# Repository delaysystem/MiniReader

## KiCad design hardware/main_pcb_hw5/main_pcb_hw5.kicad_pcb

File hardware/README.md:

# SANNI Adapters aren't compatible with MiniReader Adapters

## All the files in this directory are licensed under the Attribution 4.0 International (CC BY 4.0)     

### This means that you are free to:    
- Share - copy and redistribute the material in any medium or format    
- Adapt - remix, transform, and build upon the material for any purpose, even commercially.  

The licensor cannot revoke these freedoms as long as you follow the license terms.    

### Under the following terms:    
- Attribution - You must give appropriate credit, provide a link to the license, and indicate if changes were made. You may do so in any reasonable manner, but not in any way that suggests the licensor endorses you or your use.    
- No additional restrictions - You may not apply legal terms or technological measures that legally restrict others from doing anything the license permits.    

More details: https://creativecommons.org/licenses/by/4.0/

##

You can view the schematic and PCB files using [KiCad](https://www.kicad.org/).   
To design your own adapters you can follow this [tutorial](https://github.com/sanni/cartreader/wiki/Designing-your-own-Adapters)   
Also check out the user contributions for even more adapters: https://github.com/sanni/cartreader/discussions/354

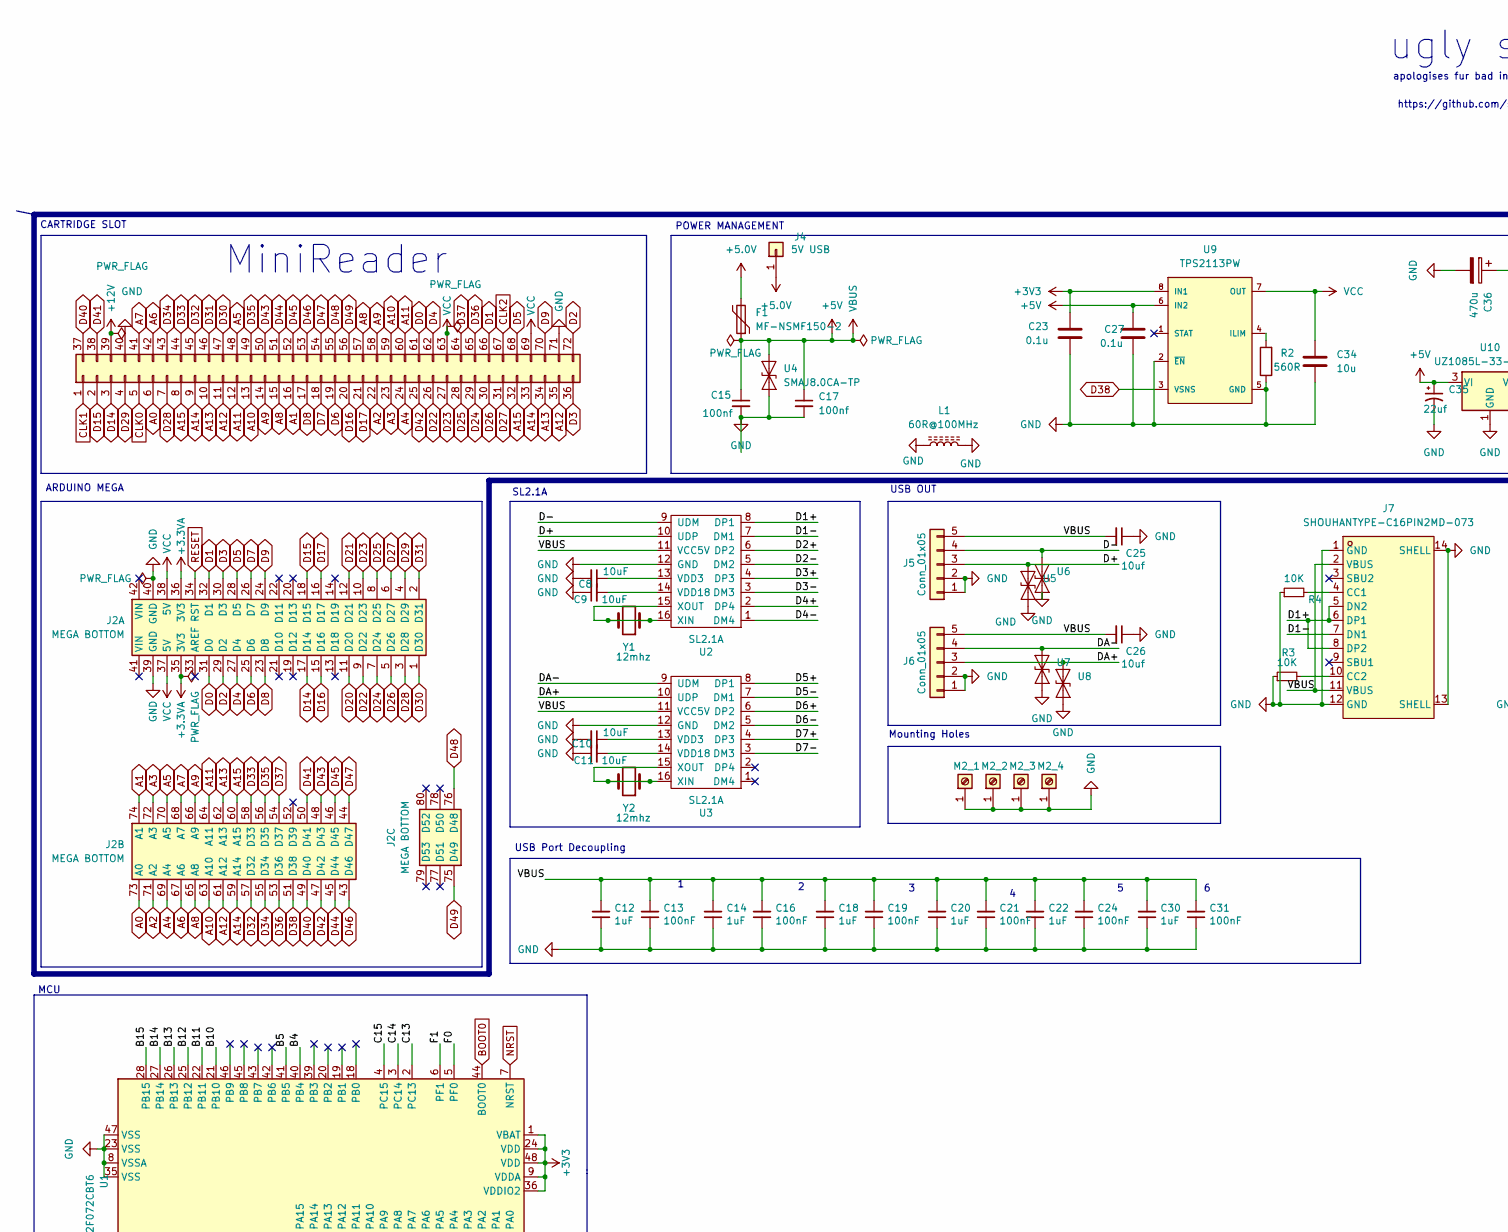
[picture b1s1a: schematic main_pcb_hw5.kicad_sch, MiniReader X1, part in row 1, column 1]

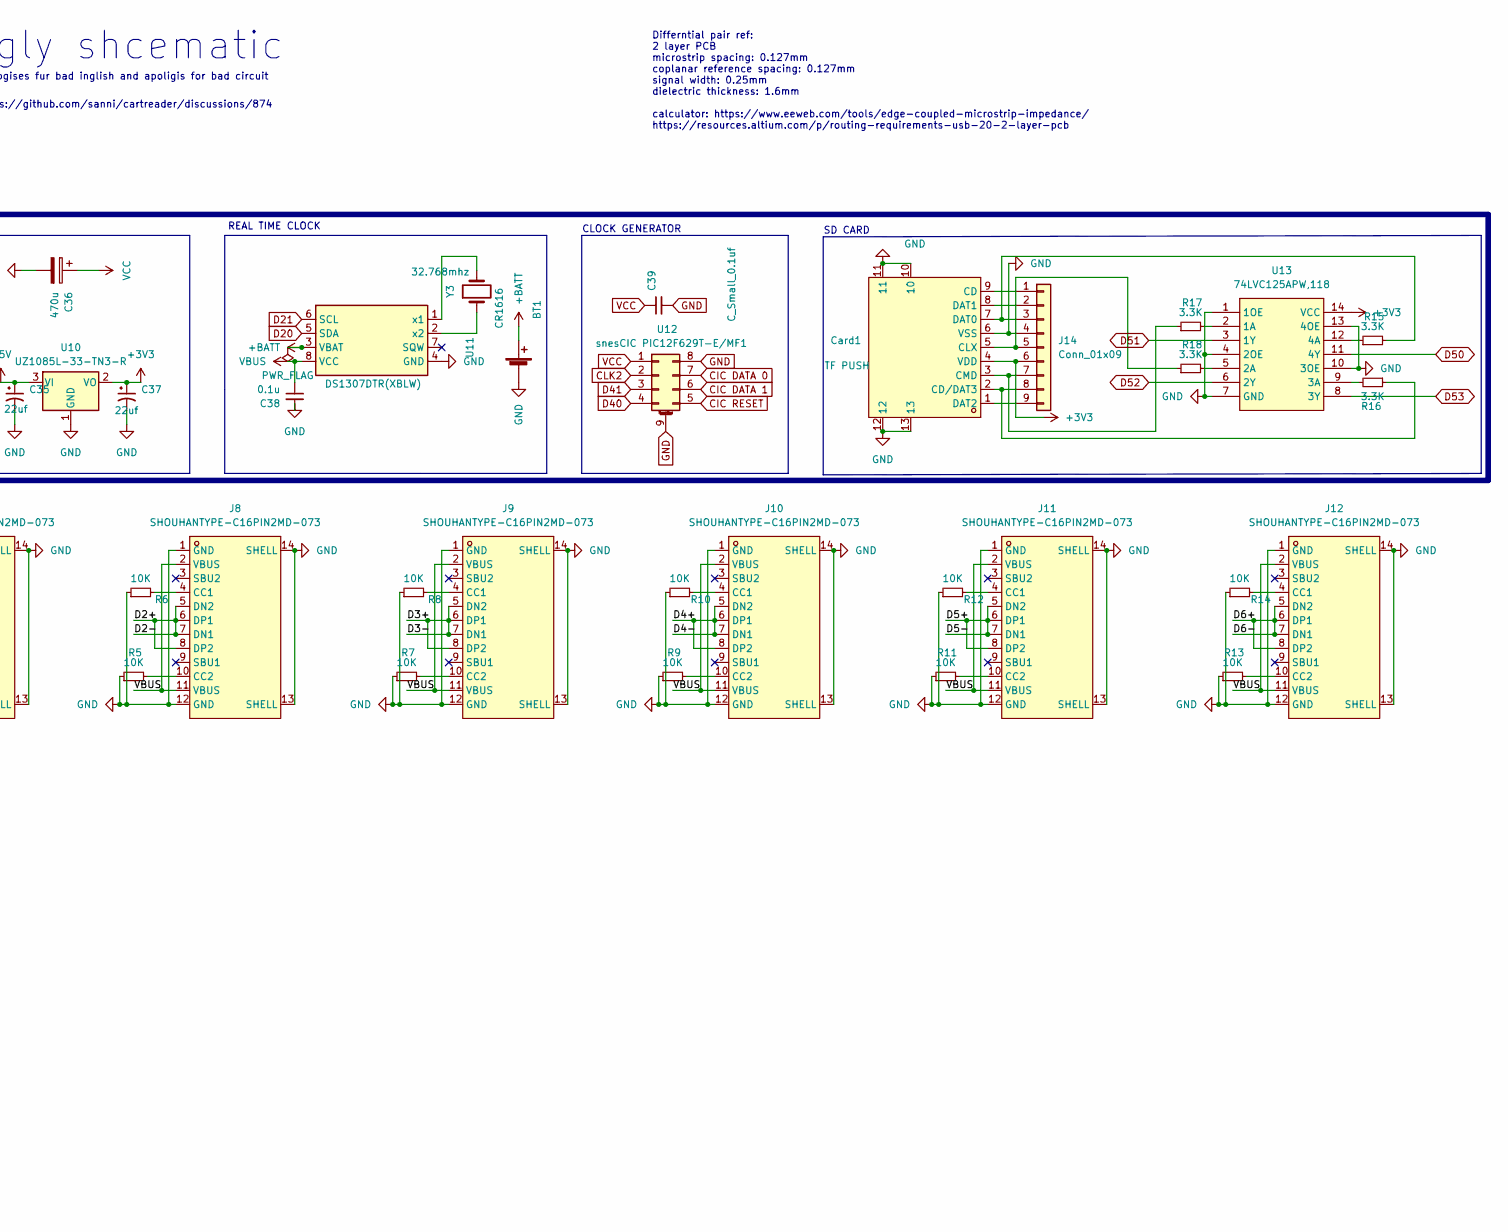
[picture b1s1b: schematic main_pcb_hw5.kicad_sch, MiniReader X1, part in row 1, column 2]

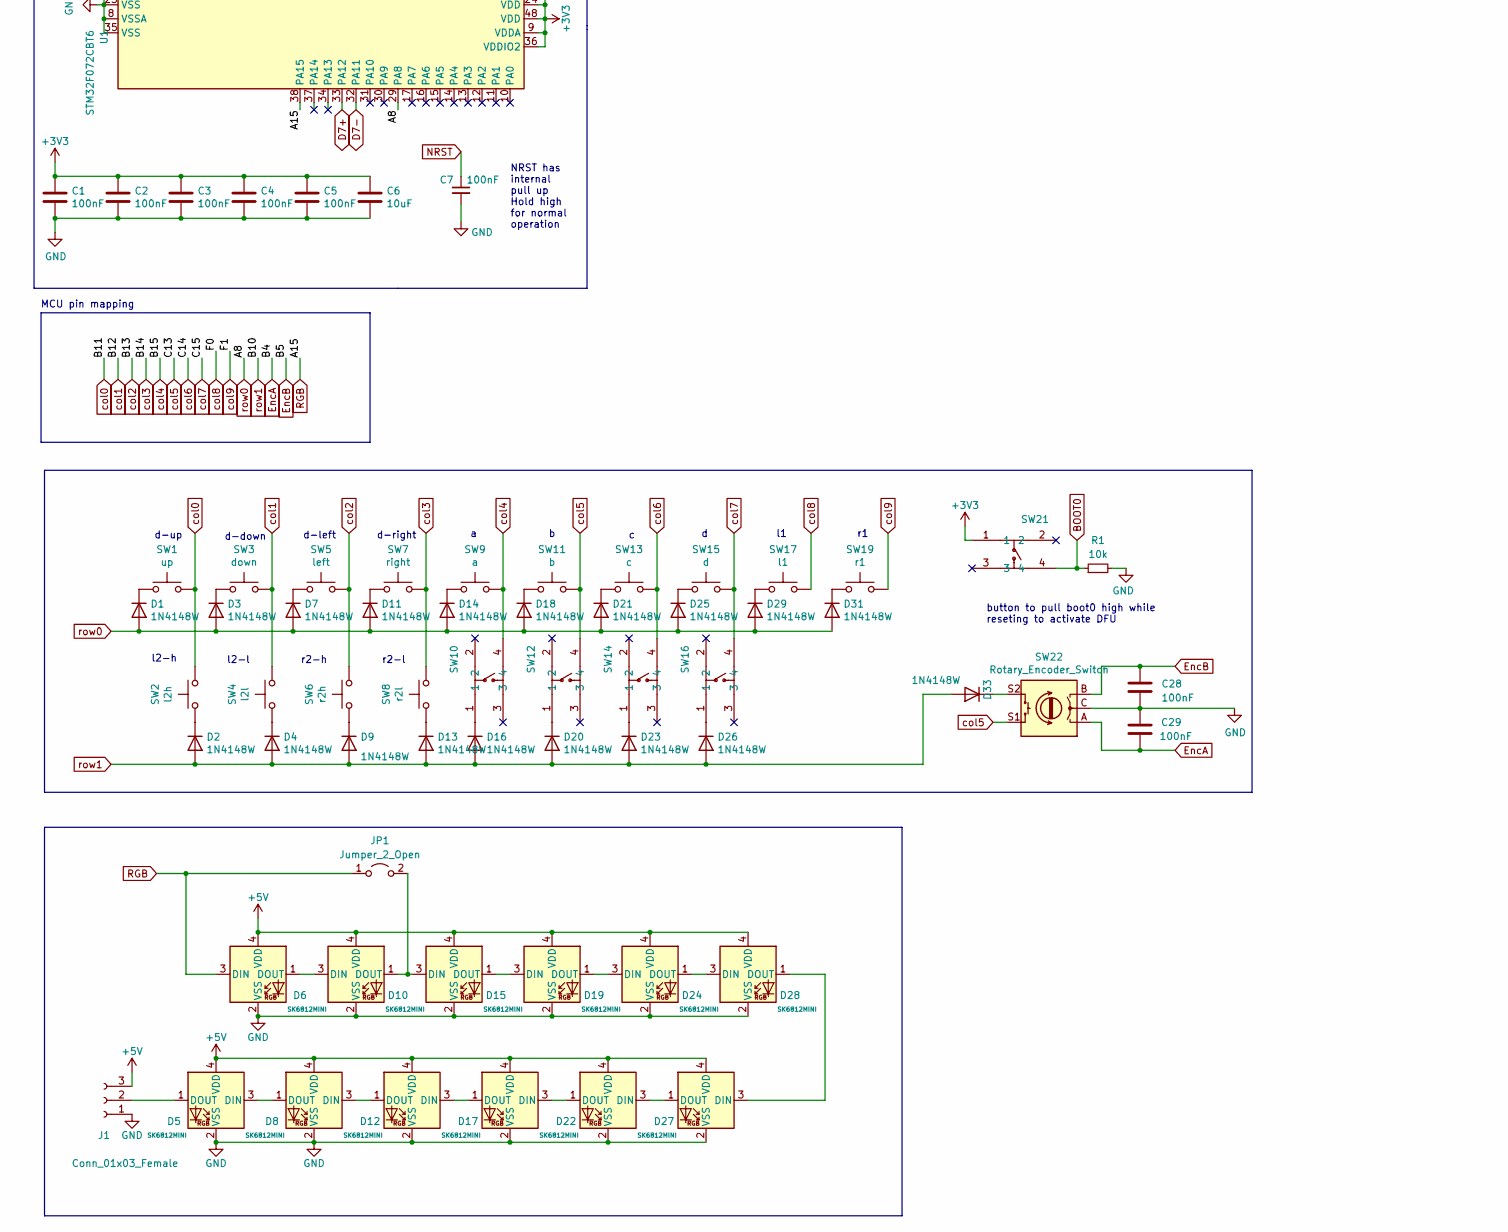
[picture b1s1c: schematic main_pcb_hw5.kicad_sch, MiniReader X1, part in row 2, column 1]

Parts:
BT1: CR1616
C1, C2, C3, C4, C5, C7, C28, C29: 100nF; C_0805_2012Metric; LCSC C307331
C6, C8, C9, C10, C11: 10uF; C_0805_2012Metric
C12, C14, C18, C20, C22, C30: 1uF; C_0805_2012Metric
C13, C16, C19, C21, C24, C31: 100nF; C_0805_2012Metric
C15, C17: 100nf; C_0805_2012Metric
C23, C27, C38: 0.1u; C_0805_2012Metric; JLCPCB C307331
C25, C26: 10uf; C_0805_2012Metric
C34: 10u; C_0805_2012Metric; JLCPCB C15525
C35, C37: 22uf; C_0805_2012Metric
C36: 470u; CP_EIA-7343-31_Kemet-D
C39: C_Small_0.1uf; C_0805_2012Metric
Card1: TF PUSH; TF-SMD_TF-PUSH; LCSC Part C393941
D1, D2, D3, D4, D7, D9, D11, D13, D14, D16, D20, D23, D26: 1N4148W; D_SOD-123; JlcRotOffset 14
D5, D12, D17: SK6812MINI; LED_SK6812MINI_PLCC4_3.5x3.5mm_P1.75mm; JlcRotOffset 14
D6, D10: SK6812MINI; LED_SK6812MINI_PLCC4_3.5x3.5mm_P1.75mm
D8: SK6812MINI; LED_SK6812MINI_PLCC4_3.5x3.5mm_P1.75mm; JlcRotOffset 194
D15, D24, D27, D28: SK6812MINI; LED_SK6812MINI_PLCC4_3.5x3.5mm_P1.75mm; JlcRotOffset -14
D18, D21, D25, D29, D31: 1N4148W; D_SOD-123; JlcRotOffset -14
D19: SK6812MINI; LED_SK6812MINI_PLCC4_3.5x3.5mm_P1.75mm; JlcRotOffset 166
D22: SK6812MINI; LED_SK6812MINI_PLCC4_3.5x3.5mm_P1.75mm; JlcRotOffset 180
D33: 1N4148W; D_SOD-123; JlcRotOffset 0
F1: MF-NSMF150-2; Fuse_1206_3216Metric; LCSC C135341
J1: Conn_01x03_Female; PinSocket_1x03_P2.54mm_Vertical
J2: MEGA BOTTOM; MEGA2560_PRO_EMBED_SMD
J3: Conn_02x36; Secondary_Board_Connector
J4: 5V USB; TestPoint_Pad_D2.0mm
J5, J6: Conn_01x05; PinHeader_1x05_P1.00mm_Vertical
J7, J8, J9, J10, J11, J12: SHOUHANTYPE-C16PIN2MD-073; USB-C-SMD_TYPE-C-6PIN-2MD-073; PARTREV 4; LCSC Part C2765186
J14: Conn_01x09; PinHeader_1x09_P1.00mm_Vertical
JP1: Jumper_2_Open; SolderJumper-2_P1.3mm_Open_TrianglePad1.0x1.5mm
L1: 60R@100MHz; L_1206_3216Metric; Manufacturer Part No MLB3216-600P4A(f); LCSC C33600
M2_1, M2_2, M2_3, M2_4: Screw_Terminal_01x01; MountingHole_2.2mm_M2_ISO7380_Pad
R1: 10k; R_0805_2012Metric
R2: 560R; R_0805_2012Metric; JLCPCB C137858
R3, R4, R5, R6, R7, R8, R9, R10, R11, R12, R13, R14: 10K; R_0805_2012Metric
R15, R16, R17, R18: 3.3K; R_0805_2012Metric
SW1: up; MX-Hotswap-1U
SW2: l2h; MX-Hotswap-1U
SW3: down; MX-Hotswap-1U
SW4: l2l; MX-Hotswap-1U
SW5: left; MX-Hotswap-1U
SW6: r2h; MX-Hotswap-1U
SW7: right; MX-Hotswap-1U
SW8: r2l; MX-Hotswap-1U
SW9: a; MX-Hotswap-1U
SW10, SW12, SW14, SW16, SW21: SKQGABE010; SW-SMD_4P-L4.5-W4.5-P3.00-LS6.8; LCSC C115351
SW11: b; MX-Hotswap-1U
SW13: c; MX-Hotswap-1U
SW15: d; MX-Hotswap-1U
SW17: l1; MX-Hotswap-1U
SW19: r1; MX-Hotswap-1U
SW22: Rotary_Encoder_Switch; RotaryEncoder_EC11_no_mp
U1: STM32F072CBT6; LQFP-48_7x7mm_P0.5mm; JlcRotOffset 90
U2, U3: SL2.1A; SOIC-16_4.55x10.3mm_P1.27mm
U4, U5, U6, U7, U8: SMAJ8.0CA-TP; D_SMA
U9: TPS2113PW; TSSOP-8_4.4x3mm_P0.65mm
U10: UZ1085L-33-TN3-R; TO-252-2
U11: DS1307DTR(XBLW); SOIC-8_3.9x4.9mm_P1.27mm
U12: snesCIC PIC12F629T-E/MF1; DFN-8-1EP_4x4mm_P0.8mm_EP2.39x2.21mm
U13: 74LVC125APW,118; TSSOP-14_L5.0-W4.4-P0.65-LS6.4-BL; LCSC Part C6059
Y1, Y2: 12mhz; Crystal_HC49-4H_Vertical
Y3: 32.768mhz; Crystal_HC49-4H_Vertical

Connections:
+3.3VA: J2.35 (3V3), J2.36 (3V3)
+3V3: C1.1, C2.1, C3.1, C4.1, C5.1, C6.1, C23.2, C37.1, Card1.4 (VDD), J14.6, SW21.1, U1.1 (VBAT), U1.9 (VDDA), U1.24 (VDD), U1.36 (VDDIO2), U1.48 (VDD), U9.8 (IN1), U10.2 (VO), U13.14 (VCC)
+5.0V: F1.2, J4.1
+5V: C12.2, C13.2, C14.2, C15.1, C16.2, C17.1, C18.2, C19.2, C20.2, C21.2, C22.2, C24.2, C25.2, C26.2, C27.1, C30.2, C31.2, C35.1, C38.1, D5.4 (VDD), D6.4 (VDD), D8.4 (VDD), D10.4 (VDD), D12.4 (VDD), D15.4 (VDD), D17.4 (VDD), D19.4 (VDD), D22.4 (VDD), D24.4 (VDD), D27.4 (VDD), D28.4 (VDD), F1.1, J1.3 (Pin_1), J5.5, J6.5, J7.2 (VBUS), J7.11 (VBUS), J8.2 (VBUS), J8.11 (VBUS), J9.2 (VBUS), J9.11 (VBUS), J10.2 (VBUS), J10.11 (VBUS), J11.2 (VBUS), J11.11 (VBUS), J12.2 (VBUS), J12.11 (VBUS), U2.11 (VCC5V), U3.11 (VCC5V), U4.2 (A2), U9.6 (IN2), U10.3 (VI), U11.8 (VCC)
+12V: J3.39
+BATT: BT1.1 (+), U11.3 (VBAT)
/D1+: J7.5 (DN2), J7.6 (DP1), J7.8 (DP2), U2.8 (DP1)
/D1-: J7.7 (DN1), U2.7 (DM1)
/D2+: J8.5 (DN2), J8.6 (DP1), J8.7 (DN1), J8.8 (DP2), U2.5 (DM2), U2.6 (DP2)
/D3+: J9.5 (DN2), J9.6 (DP1), J9.7 (DN1), J9.8 (DP2), U2.3 (DM3), U2.4 (DP3)
/D4+: J10.5 (DN2), J10.6 (DP1), J10.7 (DN1), J10.8 (DP2), U2.1 (DM4), U2.2 (DP4)
/D5+: J11.5 (DN2), J11.6 (DP1), J11.7 (DN1), J11.8 (DP2), U3.7 (DM1), U3.8 (DP1)
/D6+: J12.5 (DN2), J12.6 (DP1), J12.7 (DN1), J12.8 (DP2), U3.5 (DM2), U3.6 (DP2)
/D+: J5.3, U2.10 (UDP), U5.2 (A2)
/D-: J5.4, U2.9 (UDM), U6.2 (A2)
/DA+: J6.3, U3.10 (UDP), U8.2 (A2)
/DA-: J6.4, U3.9 (UDM), U7.2 (A2)
A0: J2.73 (A0), J3.6
A1: J2.74 (A1), J3.16
A2: J2.71 (A2), J3.22
A3: J2.72 (A3), J3.23
A4: J2.69 (A4), J3.24
A5: J2.70 (A5), J3.48
A6: J2.67 (A6), J3.42
A7: J2.68 (A7), J3.41
A8: D1.2 (A), D3.2 (A), D7.2 (A), D11.2 (A), D14.2 (A), D18.2 (A), D21.2 (A), D25.2 (A), D29.2 (A), D31.2 (A), J2.65 (A8), J3.15, J3.57, U1.29 (PA8)
A9: J2.66 (A9), J3.14, J3.58
A10: J2.63 (A10), J3.13, J3.59
A11: J2.64 (A11), J3.12, J3.60
A12: J2.61 (A12), J3.11, J3.35
A13: J2.62 (A13), J3.10, J3.34
A14: J2.59 (A14), J3.9, J3.33
A15: D6.3 (DIN), J2.60 (A15), J3.8, J3.32, JP1.1 (A), U1.38 (PA15)
BOOT0: R1.1, SW21.4, U1.44 (BOOT0)
CIC DATA 0: U12.7
CIC DATA 1: U12.6
CIC RESET: U12.5
CLK0: J3.5
CLK1: J3.1
CLK2: J3.67, U12.2
D0: J2.31 (D0), J3.61
D1: J2.32 (D1), J3.66
D2: J2.29 (D2), J3.72
D3: J2.30 (D3), J3.36
D4: J2.27 (D4), J3.62
D5: J2.28 (D5), J3.68
D6: J2.25 (D6), J3.19
D7: J2.26 (D7), J3.18
D7+: U1.33 (PA12), U3.4 (DP3)
D7-: U1.32 (PA11), U3.3 (DM3)
D8: J2.23 (D8), J3.17
D9: J2.24 (D9), J3.70
D14: J2.17 (D14), J3.3
D15: J2.18 (D15), J3.2
D16: J2.15 (D16), J3.20
D17: J2.16 (D17), J3.21
D20: J2.11 (D20), U11.5 (SDA)
D21: J2.12 (D21), U11.6 (SCL)
D22: J2.9 (D22), J3.26
D23: J2.10 (D23), J3.27
D24: J2.7 (D24), J3.29
D25: J2.8 (D25), J3.28
D26: J2.5 (D26), J3.30
D27: J2.6 (D27), J3.31
D28: J2.3 (D28), J3.7
D29: J2.4 (D29), J3.4
D30: J2.1 (D30), J3.47
D31: J2.2 (D31), J3.46
D32: J2.57 (D32), J3.45
D33: J2.58 (D33), J3.44
D34: J2.55 (D34), J3.43
D35: J2.56 (D35), J3.49
D36: J2.53 (D36), J3.65
D37: J2.54 (D37), J3.64
D38: J2.51 (D38), U9.3 (VSNS)
D40: J2.49 (D40), J3.37, U12.4
D41: J2.50 (D41), J3.38, U12.3
D42: J2.47 (D42), J3.25
D43: J2.48 (D43), J3.50
D44: J2.45 (D44), J3.51
D45: J2.46 (D45), J3.52
D46: J2.43 (D46), J3.53
D47: J2.44 (D47), J3.54
D48: J2.76 (D48), J3.55
D49: J2.75 (D49), J3.56
D50: U13.11 (4Y)
D51: U13.3 (1Y)
D52: U13.6 (2Y)
D53: U13.8 (3Y)
EncA: C29.1, SW22.A, U1.40 (PB4)
EncB: C28.1, SW22.B, U1.41 (PB5)
GND: BT1.2 (-), C1.2, C2.2, C3.2, C4.2, C5.2, C6.2, C7.2, C8.2, C9.1, C10.2, C11.1, C12.1, C13.1, C14.1, C15.2, C16.1, C17.2, C18.1, C19.1, C20.1, C21.1, C22.1, C23.1, C24.1, C25.1, C26.1, C27.2, C28.2, C29.2, C30.1, C31.1, C34.2, C35.2, C36.2, C37.2, C38.2, C39.2, Card1.6 (VSS), Card1.10, Card1.11, Card1.12, Card1.13, D5.2 (VSS), D6.2 (VSS), D8.2 (VSS), D10.2 (VSS), D12.2 (VSS), D15.2 (VSS), D17.2 (VSS), D19.2 (VSS), D22.2 (VSS), D24.2 (VSS), D27.2 (VSS), D28.2 (VSS), J1.1 (Pin_3), J2.39 (GND), J2.40 (GND), J3.40, J3.71, J5.1, J5.2, J6.1, J6.2, J7.1 (GND), J7.12 (GND), J7.13 (SHELL), J7.14 (SHELL), J8.1 (GND), J8.12 (GND), J8.13 (SHELL), J8.14 (SHELL), J9.1 (GND), J9.12 (GND), J9.13 (SHELL), J9.14 (SHELL), J10.1 (GND), J10.12 (GND), J10.13 (SHELL), J10.14 (SHELL), J11.1 (GND), J11.12 (GND), J11.13 (SHELL), J11.14 (SHELL), J12.1 (GND), J12.12 (GND), J12.13 (SHELL), J12.14 (SHELL), J14.4, L1.1, L1.2, M2_1.1, M2_2.1, M2_3.1, M2_4.1, R1.2, R2.1, R3.1, R4.1, R5.1, R6.1, R7.1, R8.1, R9.1, R10.1, R11.1, R12.1, R13.1, R14.1, SW22.C, U1.8 (VSSA), U1.23 (VSS), U1.35 (VSS), U1.47 (VSS), U2.12 (GND), U3.12 (GND), U4.1 (A1), U5.1 (A1), U6.1 (A1), U7.1 (A1), U8.1 (A1), U9.2 (~EN), U9.5 (GND), U10.1 (GND), U11.4 (GND), U12.8, U12.9 (MountPin), U13.1 (1OE), U13.4 (2OE), U13.7 (GND), U13.10 (3OE), U13.13 (4OE)
NRST: C7.1, U1.7 (NRST)
unnamed: Card1.9 (CD), J14.1
unnamed: Card1.2 (CD/DAT3), J14.8, R16.1
unnamed: Card1.5 (CLX), J14.5, R18.1
unnamed: Card1.3 (CMD), J14.7, R17.1
unnamed: Card1.7 (DAT0), J14.3, R15.2
unnamed: Card1.8 (DAT1), J14.2
unnamed: Card1.1 (DAT2), J14.9
unnamed: D1.1 (K), SW1.1
unnamed: D2.1 (K), SW2.1
unnamed: D3.1 (K), SW3.1
unnamed: D4.1 (K), SW4.1
unnamed: D5.3 (DIN), D8.1 (DOUT)
unnamed: D5.1 (DOUT), J1.2
unnamed: D7.1 (K), SW5.1
unnamed: D9.1 (K), SW6.1
unnamed: D6.1 (DOUT), D10.3 (DIN)
unnamed: D10.1 (DOUT), D15.3 (DIN), JP1.2 (B)
unnamed: D11.1 (K), SW7.1
unnamed: D12.3 (DIN), D17.1 (DOUT)
unnamed: D8.3 (DIN), D12.1 (DOUT)
unnamed: D13.1 (K), SW8.1
unnamed: D14.1 (K), SW9.1
unnamed: D15.1 (DOUT), D19.3 (DIN)
unnamed: D16.1 (K), SW10.1
unnamed: D17.3 (DIN), D22.1 (DOUT)
unnamed: D18.1 (K), SW11.1
unnamed: D19.1 (DOUT), D24.3 (DIN)
unnamed: D20.1 (K), SW12.1
unnamed: D21.1 (K), SW13.1
unnamed: D22.3 (DIN), D27.1 (DOUT)
unnamed: D23.1 (K), SW14.1
unnamed: D24.1 (DOUT), D28.3 (DIN)
unnamed: D25.1 (K), SW15.1
unnamed: D26.1 (K), SW16.1
unnamed: D27.3 (DIN), D28.1 (DOUT)
unnamed: D29.1 (K), SW17.1
unnamed: D31.1 (K), SW19.1
unnamed: D33.1 (K), SW22.S2
unnamed: J7.4 (CC1), R4.2
unnamed: J7.10 (CC2), R3.2
unnamed: J8.4 (CC1), R6.2
unnamed: J8.10 (CC2), R5.2
unnamed: J9.4 (CC1), R8.2
unnamed: J9.10 (CC2), R7.2
unnamed: J10.4 (CC1), R10.2
unnamed: J10.10 (CC2), R9.2
unnamed: J11.4 (CC1), R12.2
unnamed: J11.10 (CC2), R11.2
unnamed: J12.4 (CC1), R14.2
unnamed: J12.10 (CC2), R13.2
unnamed: C8.1, U2.13 (VDD3)
unnamed: C9.2, U2.14 (VDD18)
unnamed: U2.15 (XOUT), U2.16 (XIN), Y1.1, Y1.2
unnamed: C10.1, U3.13 (VDD3)
unnamed: C11.2, U3.14 (VDD18)
unnamed: U3.15 (XOUT), U3.16 (XIN), Y2.1, Y2.2
unnamed: R2.2, U9.4 (ILIM)
unnamed: U11.1 (x1), Y3.2
unnamed: U11.2 (x2), Y3.1
unnamed: R17.2, U13.2 (1A)
unnamed: R18.2, U13.5 (2A)
unnamed: R16.2, U13.9 (3A)
unnamed: R15.1, U13.12 (4A)
RESET: J2.34 (RST)
VCC: C34.1, C36.1, C39.1, J2.37 (5V), J2.38 (5V), J3.63, J3.69, U9.7 (OUT), U12.1
col0: SW1.2, SW2.2, U1.22 (PB11)
col1: SW3.2, SW4.2, U1.25 (PB12)
col2: SW5.2, SW6.2, U1.26 (PB13)
col3: SW7.2, SW8.2, U1.27 (PB14)
col4: SW9.2, SW10.4, U1.28 (PB15)
col5: SW11.2, SW12.4, SW22.S1, U1.2 (PC13)
col6: SW13.2, SW14.4, U1.3 (PC14)
col7: SW15.2, SW16.4, U1.4 (PC15)
col8: SW17.2, U1.5 (PF0)
col9: SW19.2, U1.6 (PF1)
row1: D2.2 (A), D4.2 (A), D9.2 (A), D13.2 (A), D16.2 (A), D20.2 (A), D23.2 (A), D26.2 (A), D33.2 (A), U1.21 (PB10)

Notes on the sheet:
SD CARD
r2-h
SL2.1A
d-up
NRST has internal pull up Hold high for normal operation
l2-h
REAL TIME CLOCK
button to pull boot0 high while reseting to activate DFU
CLOCK GENERATOR
r2-l
MCU
Differntial pair ref: 2 layer PCB microstrip spacing: 0.127mm coplanar reference spacing: 0.127mm signal width: 0.25mm dielectric thickness: 1.6mm calculator: https://www.eeweb.com/tools/edge-coupled-microstrip-impedance/ https://resources.altium.com/p/routing-requirements-usb-20-2-layer-pcb
d-down
https://github.com/sanni/cartreader/discussions/874
MiniReader
d-left
POWER MANAGEMENT
ARDUINO MEGA
ugly shcematic
MCU pin mapping
Mounting Holes
apologises fur bad inglish and apoligis for bad circuit
l2-l
USB OUT
CARTRIDGE SLOT
USB Port Decoupling
d-right

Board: 2 copper layers, 144 parts (48 on the bottom side), 158 nets, no tracks yet.

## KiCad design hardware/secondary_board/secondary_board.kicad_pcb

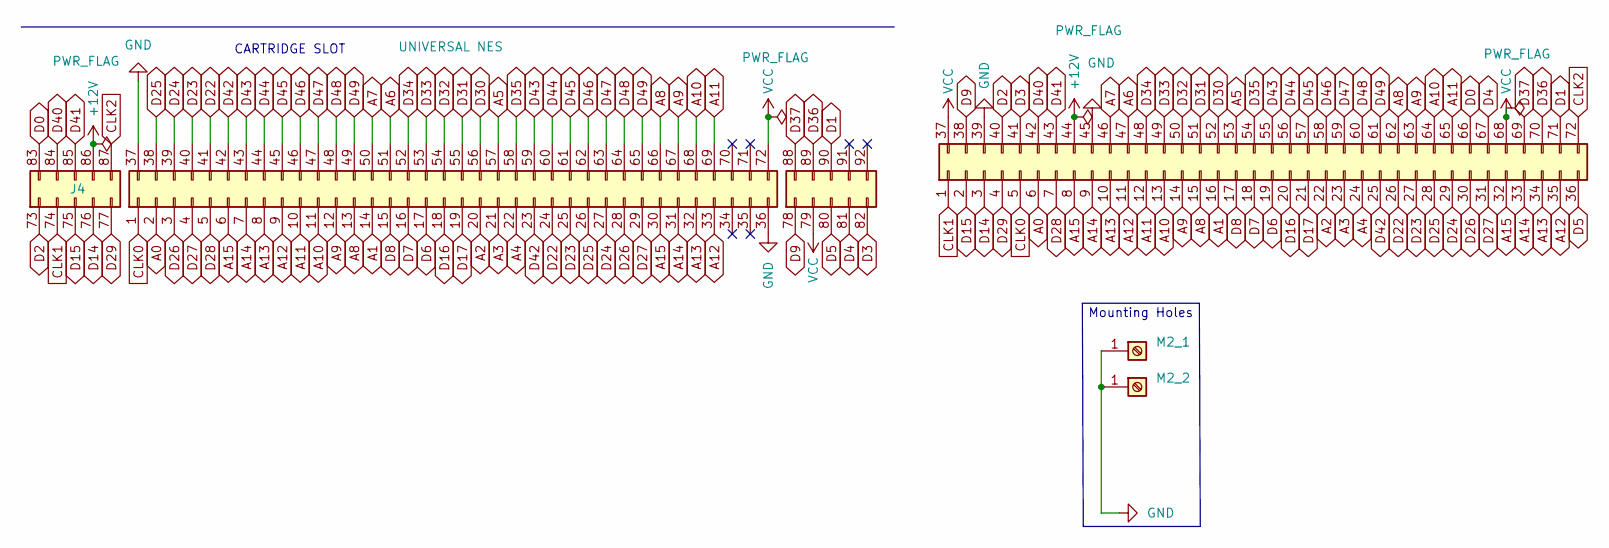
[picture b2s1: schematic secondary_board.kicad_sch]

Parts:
J1: Conn_01x72; PinHeader_1x72_P1.00mm_Vertical
J4: UNIVERSAL NES; UNIVERSAL_NES
M2_1, M2_2: Screw_Terminal_01x01; MountingHole_2.2mm_M2_ISO7380_Pad

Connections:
+12V: J1.44, J4.86
A0: J1.6, J4.2
A1: J1.16, J4.14
A2: J1.22, J4.20
A3: J1.23, J4.21
A4: J1.24, J4.22
A5: J1.53, J4.57
A6: J1.47, J4.51
A7: J1.46, J4.50
A8: J1.15, J1.62, J4.13, J4.66
A9: J1.14, J1.63, J4.12, J4.67
A10: J1.13, J1.64, J4.11, J4.68
A11: J1.12, J1.65, J4.10, J4.69
A12: J1.11, J1.35, J4.9, J4.33
A13: J1.10, J1.34, J4.8, J4.32
A14: J1.9, J1.33, J4.7, J4.31
A15: J1.8, J1.32, J4.6, J4.30
CLK0: J1.5, J4.1
CLK1: J1.1, J4.74
CLK2: J1.72, J4.87
D0: J1.66, J4.83
D1: J1.71, J4.90
D2: J1.40, J4.73
D3: J1.41, J4.82
D4: J1.67, J4.81
D5: J1.36, J4.80
D6: J1.19, J4.17
D7: J1.18, J4.16
D8: J1.17, J4.15
D9: J1.38, J4.78
D14: J1.3, J4.76
D15: J1.2, J4.75
D16: J1.20, J4.18
D17: J1.21, J4.19
D22: J1.26, J4.24, J4.41
D23: J1.27, J4.25, J4.40
D24: J1.29, J4.27, J4.39
D25: J1.28, J4.26, J4.38
D26: J1.30, J4.3, J4.28
D27: J1.31, J4.4, J4.29
D28: J1.7, J4.5
D29: J1.4, J4.77
D30: J1.52, J4.56
D31: J1.51, J4.55
D32: J1.50, J4.54
D33: J1.49, J4.53
D34: J1.48, J4.52
D35: J1.54, J4.58
D36: J1.70, J4.89
D37: J1.69, J4.88
D40: J1.42, J4.84
D41: J1.43, J4.85
D42: J1.25, J4.23, J4.42
D43: J1.55, J4.43, J4.59
D44: J1.56, J4.44, J4.60
D45: J1.57, J4.45, J4.61
D46: J1.58, J4.46, J4.62
D47: J1.59, J4.47, J4.63
D48: J1.60, J4.48, J4.64
D49: J1.61, J4.49, J4.65
GND: J1.39, J1.45, J4.36, J4.37, M2_1.1, M2_2.1
VCC: J1.37, J1.68, J4.72, J4.79

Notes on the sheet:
Mounting Holes
CARTRIDGE SLOT

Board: 2 copper layers, 4 parts (0 on the bottom side), 62 nets, no tracks yet.

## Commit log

2024-07-18 cliche commit summary goes here
